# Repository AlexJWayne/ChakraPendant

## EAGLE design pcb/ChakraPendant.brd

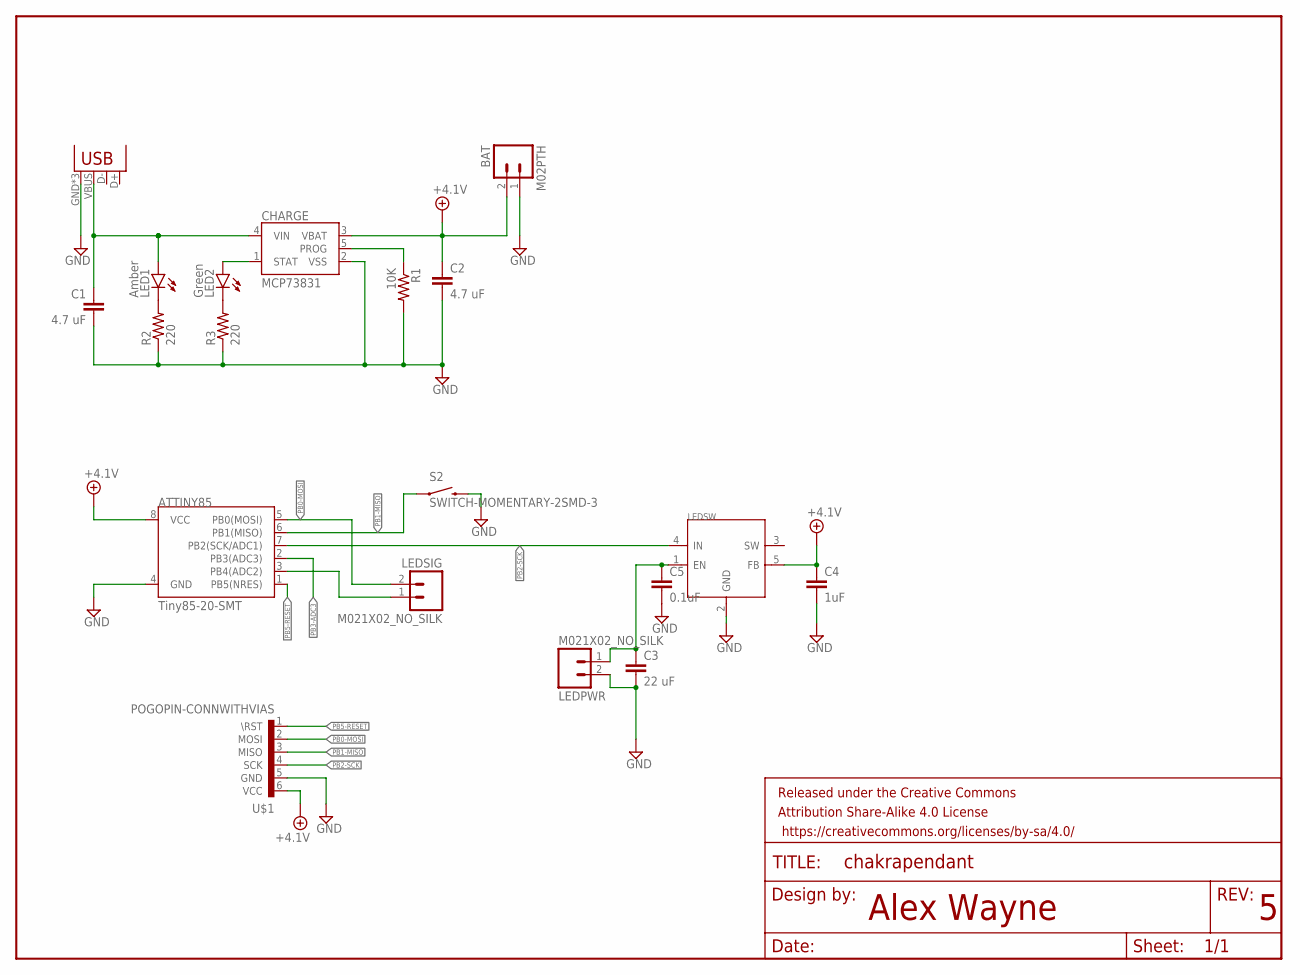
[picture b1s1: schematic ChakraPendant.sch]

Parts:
ATTINY85: Tiny85-20-SMT; SO08-EIAJ
BAT: M02PTH; 1X02
C1, C2: 4.7 uF; 0603-CAP
C3: 22 uF; 1206
C4: 1uF; 0603-CAP
C5: 0.1uF; 0603-CAP
CHARGE: MCP73831; SOT23-5
FRAME1: FRAME-LETTER; CREATIVE_COMMONS
JP1: USB-MICROB
LED1: Amber; LED-0603
LED2: Green; LED-0603
LEDPWR: M021X02_NO_SILK; 1X02_NO_SILK
LEDSIG: M021X02_NO_SILK; 1X02_NO_SILK
LEDSW: ETA3406; SOT23-5
R1: 10K; 0603-RES
R2, R3: 220; 0603-RES
S2: SWITCH-MOMENTARY-2SMD-3; TACTILE_SWITCH_SMD-3
U$1: POGOPIN-CONNWITHVIAS; POGOPROG-CONN-0H

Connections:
+4.1V: ATTINY85.8 (VCC), BAT.2, C2.1, C4.1, CHARGE.3 (VBAT), LEDSW.5 (FB), U$1.6 (VCC)
GND: ATTINY85.4 (GND), BAT.1, C1.2, C2.2, C3.2, C4.2, C5.2, CHARGE.2 (VSS), JP1.GND, JP1.MT1 (GND), JP1.MT2 (GND), LEDPWR.2, LEDSW.2 (GND), R1.2, R2.1, R3.1, S2.4 (2), U$1.5 (GND)
unnamed: ATTINY85.3 (PB4(ADC2)), LEDSIG.1
unnamed: LED1.C, R2.2
unnamed: LED2.C, R3.2
unnamed: C3.1, C5.1, LEDPWR.1, LEDSW.1 (EN)
PB0-MOSI: ATTINY85.5 (PB0(MOSI)), LEDSIG.2, U$1.2 (MOSI)
PB1-MISO: ATTINY85.6 (PB1(MISO)), S2.1, U$1.3 (MISO)
PB2-SCK: ATTINY85.7 (PB2(SCK/ADC1)), LEDSW.4 (IN), U$1.4 (SCK)
PB3-ADC3: ATTINY85.2 (PB3(ADC3))
PB5-RESET: ATTINY85.1 (PB5(NRES)), U$1.1 (\RST)
PROG: CHARGE.5 (PROG), R1.1
STAT: CHARGE.1 (STAT), LED2.A
USB5V: C1.1, CHARGE.4 (VIN), JP1.VBUS, LED1.A

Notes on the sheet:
Alex Wayne

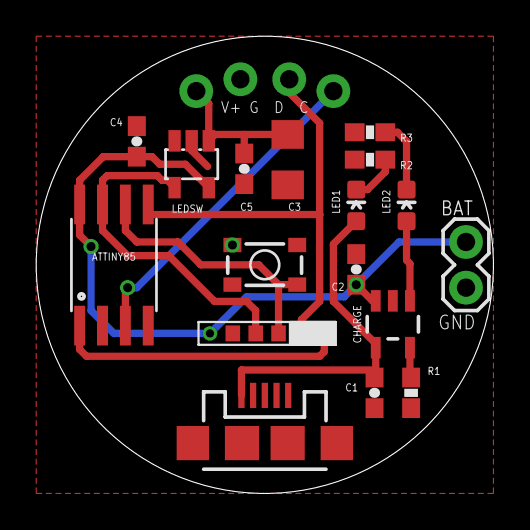
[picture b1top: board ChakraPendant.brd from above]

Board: 2 copper layers, 25.4 x 25.4 mm, 20 parts (0 on the bottom side), 13 nets.

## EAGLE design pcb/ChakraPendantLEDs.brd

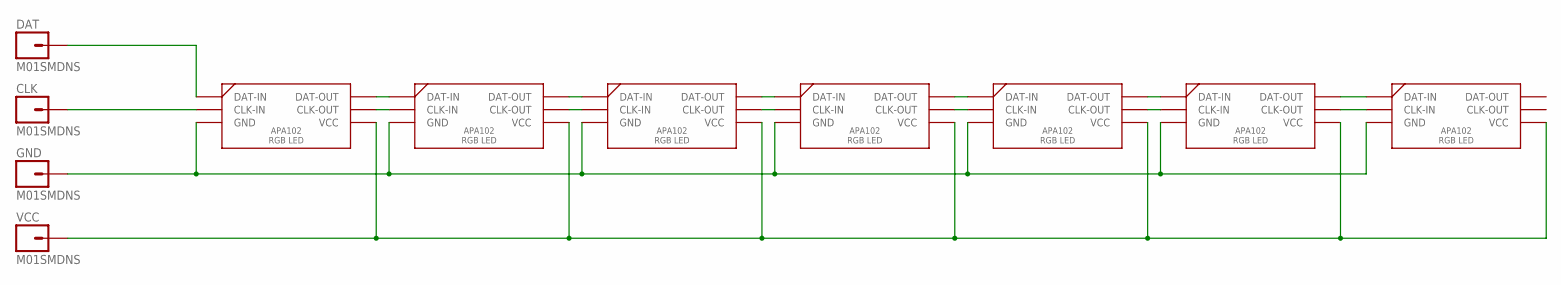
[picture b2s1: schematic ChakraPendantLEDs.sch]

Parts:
CLK: M01SMDNS; 1X01NS
DAT: M01SMDNS; 1X01NS
GND: M01SMDNS; 1X01NS
U$1, U$2, U$3, U$4, U$5, U$6, U$7: APA102; APA102_5050_LED
VCC: M01SMDNS; 1X01NS

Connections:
CLK: CLK.1, U$1.CLK-IN
DAT: DAT.1, U$1.DAT-IN
GND: GND.1, U$1.GND, U$2.GND, U$3.GND, U$4.GND, U$5.GND, U$6.GND, U$7.GND
unnamed: U$3.CLK-OUT, U$4.CLK-IN
unnamed: U$3.DAT-OUT, U$4.DAT-IN
unnamed: U$1.DAT-OUT, U$2.DAT-IN
unnamed: U$1.CLK-OUT, U$2.CLK-IN
unnamed: U$2.DAT-OUT, U$3.DAT-IN
unnamed: U$2.CLK-OUT, U$3.CLK-IN
unnamed: U$4.CLK-OUT, U$5.CLK-IN
unnamed: U$4.DAT-OUT, U$5.DAT-IN
unnamed: U$5.DAT-OUT, U$6.DAT-IN
unnamed: U$5.CLK-OUT, U$6.CLK-IN
unnamed: U$6.CLK-OUT, U$7.CLK-IN
unnamed: U$6.DAT-OUT, U$7.DAT-IN
VCC: U$1.VCC, U$2.VCC, U$3.VCC, U$4.VCC, U$5.VCC, U$6.VCC, U$7.VCC, VCC.1

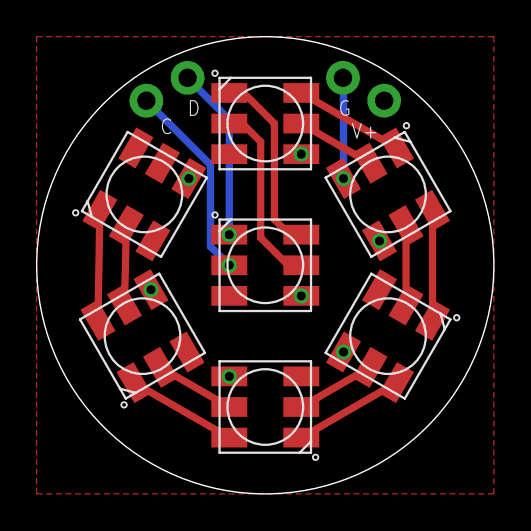
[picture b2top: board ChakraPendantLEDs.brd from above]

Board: 2 copper layers, 25.4 x 25.4 mm, 11 parts (0 on the bottom side), 16 nets.

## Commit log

2014-11-20 nitial commit
2014-12-07 Separate animation programs for each chakra.
2014-12-08 Deeper chakra1 fade
2014-12-10 Fix that PB0 and PB1 were swapped from breadboard prototype
2014-12-10 Arduino version with Fast LED
2014-12-11 Move to Arduino based program
2014-12-11 Add third enclosure design, Open SCAD based.
2014-12-11 Body added to enclosure, complete with a battery guide and diffuser bezel
2014-12-15 use internal pull up resistor for button
2014-12-15 Precision enclosure.
2014-12-16 A third chakra animation
2014-12-20 Chakra 5!
2014-12-20 Add PCB files.
2014-12-20 Chakra 6 animation and a bunch of minor tweaks.
2014-12-20 Cleanup enclosure files and widen chain channel
2014-12-20 remove not very exciting non-Arduino version
2014-12-20 this shouldn't be here
2014-12-20 Widen chain channel properly and chamfer the edge a bit.
2014-12-21 More chamfer on the top edge
2014-12-21 Save the materials so they can easily be referenced.
2014-12-21 solder paste stencil for PCB.
2014-12-21 Thicken some PCB traces
2014-12-22 reduce bevel size
2014-12-22 Chakra 7 animation and a bunch of tweaks to other animations
2015-01-09 Software sleep. Death to PWR slide switches!
2015-01-09 Remove power switches. Add Charge LEDs. Change ISP header to pogopin programmer.
2015-01-09 PCB for LEDs
2015-01-10 Flip the terminals, because they will be mirrored.
2015-01-11 GREATLY cleaned up main board schematic. Piped charge STAT to chip
2015-01-12 Upgrade LED part
2015-01-21 Turn of power to LEDs when sleeping.
2015-01-21 Fix that MOSFET was wired backwards :(
2015-01-23 Use APA102 LEDs.
    Those bastards are bright!
2015-01-23 Swap clock and data. Oops.
2015-03-10 WHO THE HELL KNOWS?
2015-04-06 Move to Attiny 84. Tweak animation timings to suck less. Added a demo mode that cycles modes.
2015-04-06 Freecad enclosure
2015-04-06 Cleanup
2015-04-06 If you change modes in cycle mode, reset the cycling timer so it doesn't change modes immediately after
2015-04-19 Refactor pendant guts into a class that can be easily instantiated. The only thing the user should need to care about is animations.
2015-04-19 cleanup LED diagram.
2015-04-19 update this soon.
2015-04-26 update enclodure
2018-08-28 enclosure updates
2018-08-28 Improve chakra 3 animation

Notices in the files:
parts and their libraries:
SparkFun-DigitalIC: Licensing: Creative Commons ShareAlike 4.0 International - https://creativecommons.org/licenses/by-sa/4.0
SparkFun-Aesthetics: Released under the Creative Commons Attribution Share-Alike 4.0 License
SparkFun-Aesthetics: https://creativecommons.org/licenses/by-sa/4.0
